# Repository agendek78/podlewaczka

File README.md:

# ESP8266 based Web meteo + irrigation system

Some web screens (Polish language):

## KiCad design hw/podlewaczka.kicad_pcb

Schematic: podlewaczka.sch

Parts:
C1, C7: 100nF; C_0603_1608Metric_Pad1.05x0.95mm_HandSolder
C3: 100nF; C_0603_1608Metric
C4: 4.7uF; C_0603_1608Metric_Pad1.05x0.95mm_HandSolder
C5: CP1; CP_Radial_D6.3mm_P2.50mm
C6, C11: 10uF; C_1210_3225Metric_Pad1.42x2.65mm_HandSolder
C8: 22uF; C_1210_3225Metric_Pad1.42x2.65mm_HandSolder
C9: 470nF; C_0603_1608Metric_Pad1.05x0.95mm_HandSolder
C10: 470uF/16V; CP_Radial_D7.5mm_P2.50mm
D1, D2, D3: SS14; D_SMB
D4: Stndby; D_0603_1608Metric_Pad1.05x0.95mm_HandSolder
D5: Charge; D_0603_1608Metric_Pad1.05x0.95mm_HandSolder
J1: UART; PinHeader_1x05_P2.54mm_Vertical
J2: Solar panel input; TerminalBlock_MetzConnect_Type059_RT06302HBWC_1x02_P3.50mm_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
J3: Battery input; PinHeader_1x03_P2.54mm_Vertical
J4: I2C Sensor connector; PinHeader_1x04_P2.54mm_Vertical
J5: Pump3; TerminalBlock_Phoenix_PT-1,5-2-3.5-H_1x02_P3.50mm_Horizontal
J6: Pump1; TerminalBlock_Phoenix_PT-1,5-2-3.5-H_1x02_P3.50mm_Horizontal
J7: Pump2; TerminalBlock_Phoenix_PT-1,5-2-3.5-H_1x02_P3.50mm_Horizontal
J8, J9, J10, J11: Screw_Terminal_01x01; MountingHole_3.2mm_M3_Pad_Via
J12: Ext IO; PinHeader_1x05_P2.54mm_Vertical
L1: 2.2uH; L_1210_3225Metric_Pad1.42x2.65mm_HandSolder
Q1, Q2, Q3: IRLML6244TRPbF; SOT-23
Q4, Q5: BC817; SOT-23
R1: 4.7M; R_0603_1608Metric_Pad1.05x0.95mm_HandSolder
R2: 1M; R_0603_1608Metric_Pad1.05x0.95mm_HandSolder
R3, R4, R5, R6, R7, R10, R11, R12, R17, R18, R22, R23: 10k; R_0603_1608Metric_Pad1.05x0.95mm_HandSolder
R8, R9: 300; R_0603_1608Metric_Pad1.05x0.95mm_HandSolder
R13: 10; R_Axial_DIN0204_L3.6mm_D1.6mm_P7.62mm_Horizontal
R14, R15, R16: 10; R_0603_1608Metric_Pad1.05x0.95mm_HandSolder
R19, R20: 1k; R_0603_1608Metric_Pad1.05x0.95mm_HandSolder
R21: 0.4R; R_1206_3216Metric
U1: ESP-12F; ESP-12E_SMD
U2: TP4056; TI_SO-PowerPAD-8
U3: SY8008; SOT-23-5

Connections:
+3V3: C3.1, C5.1, C7.1, C8.1, J4.1, J12.5, L1.2, R5.1, R6.1, R10.1, R11.1, R17.1, U1.8 (VCC)
+BATT: C4.1, D1.2, D2.2, D3.2, J3.1, J5.1, J6.1, J7.1, R1.1, R13.2, U2.5
/DTR: J1.5, Q4.2, R23.2
/RTS: J1.4, Q5.2, R22.2
/VBATT_MEAS: C1.1, R1.2, R2.1, U1.2 (ADC)
GND: C1.2, C3.2, C4.2, C5.2, C6.2, C8.2, C9.2, C10.2, C11.2, J1.1, J2.1, J3.3, J4.4, J8.1, J9.1, J10.1, J11.1, J12.1, Q1.2, Q2.2, Q3.2, R2.2, R4.2, R7.1, R12.2, R18.2, U1.9 (GND), U2.3, U2.9, U3.2 (GND)
unnamed: C7.2, R17.2, R18.1, U3.5 (FB)
unnamed: C6.1, C10.1, R13.1, U3.1 (EN), U3.4 (IN)
unnamed: D1.1, J6.2, Q1.3
unnamed: D2.1, J7.2, Q2.3
unnamed: D3.1, J5.2, Q3.3
unnamed: D4.1, R8.1
unnamed: D5.1, R9.1
unnamed: J1.2, R20.1
unnamed: J1.3, R19.1
unnamed: J2.2, R21.2
unnamed: J3.2, R3.1, R7.2, U2.1
unnamed: J12.2, Q4.3, R10.2, U1.12 (GPIO0)
unnamed: J12.3, U1.13 (GPIO4)
unnamed: J12.4, U1.14 (GPIO5)
unnamed: L1.1, U3.3 (SW)
unnamed: Q1.1, R14.1
unnamed: Q2.1, R15.1
unnamed: Q3.1, R16.1
unnamed: Q4.1, R22.1
unnamed: Q5.1, R23.1
unnamed: Q5.3, R6.2, U1.1 (REST), U1.4 (GPIO16)
unnamed: R4.1, U2.2
unnamed: R5.2, U1.3 (CH_PD)
unnamed: R8.2, U2.6
unnamed: R9.2, U2.7
unnamed: R12.1, R16.2, U1.10 (GPIO15)
unnamed: R14.2, U1.7 (GPIO13)
unnamed: R15.2, U1.6 (GPIO12)
unnamed: R19.2, U1.16 (TXD)
unnamed: R20.2, U1.15 (RXD)
SCL: J4.2, U1.5 (GPIO14)
SDA: J4.3, R11.2, U1.11 (GPIO2)
VCC: C9.1, C11.1, D4.2, D5.2, R3.2, R21.1, U2.4, U2.8

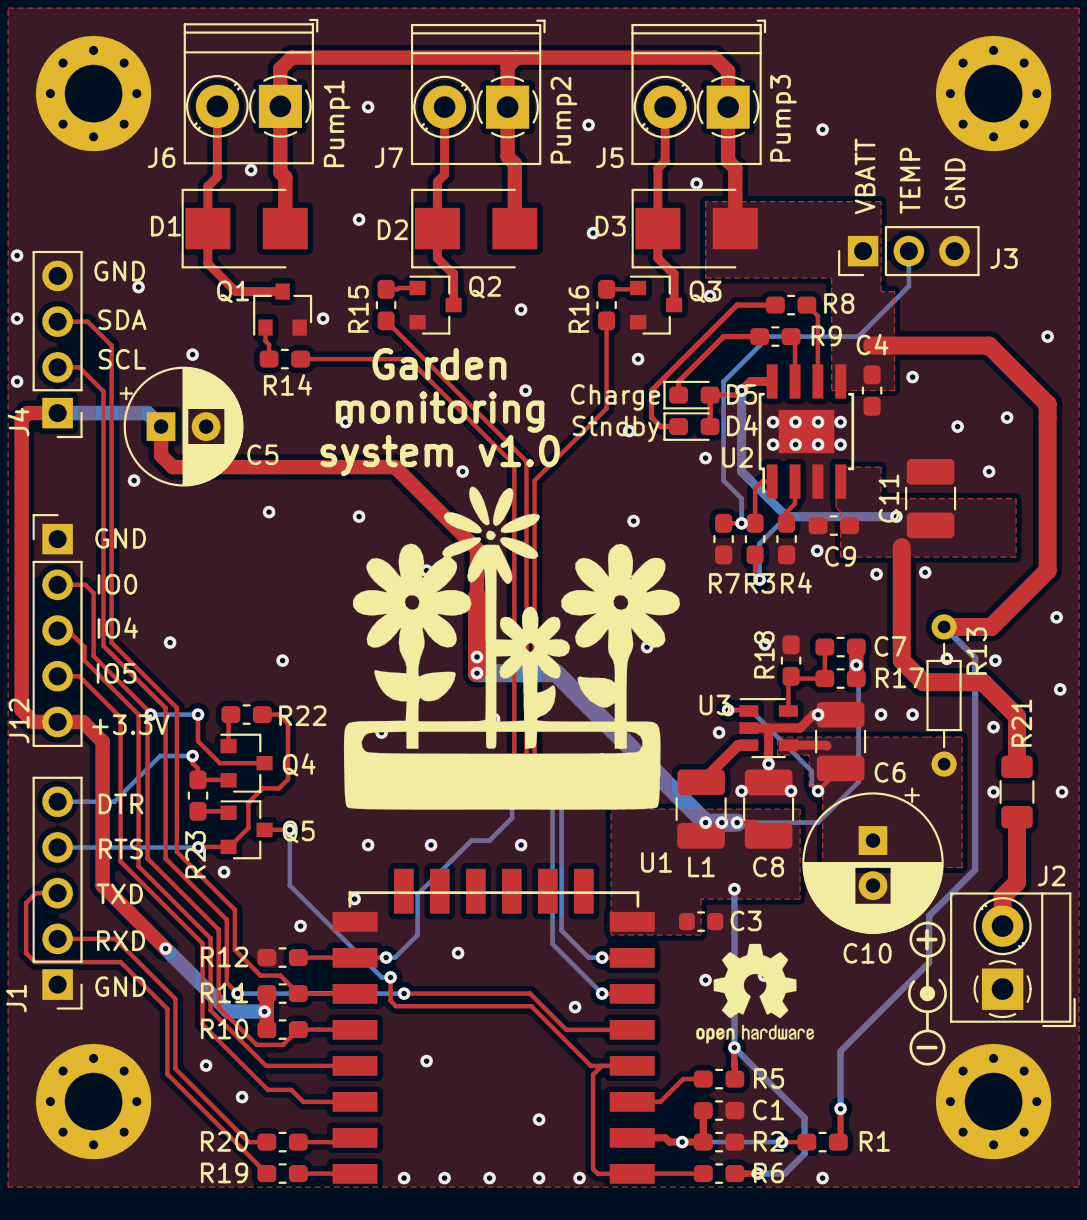
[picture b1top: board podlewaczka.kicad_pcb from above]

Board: 2 copper layers, 59 parts (0 on the bottom side), 39 nets.

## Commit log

2018-08-23 Adding read.me
2018-09-03 Bugfixing js, adding possibility to download measurement data files
2018-09-03 Adding HW
2018-09-03 PCB update
2018-09-04 Finished PCB
2018-09-05 PCB HW update
2018-11-01 Adding sleep and support for new HW
